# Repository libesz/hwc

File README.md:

# Hot Water Circulation with AVR

## The problem
This is a tiny project to control a water pump. In a typical domestic hot water system, there is a common problem that the water gets cold in the pipes if some faucets are too far. So you have to waste a lot of water (and time :) ) until you get the hot water, if is was not used recently.

The base of the solution is to build also a returning pipe between the last faucet and the boiler or hot water tank, where a pump can circulate the returning water, so that keeping the pipes hot.

The big question is that based on what event are you going to circulate the water? After a bit of googling you can find these ideas:
* Timer switch, programmed for the typical hot water use times (morning, evening).
* Thermostat: you somehow measure the returning water's temperature and control the pump when needed.
* Detect water usage: there are solutions which can detect when you use any faucet in the house. So you can trigger the circulation by using the e.g. shower for a second, than wait until the hot water arrive before you really start to use it.

## Solution
I was not impressed by any of the solutions above, even not with any combinations. Fortunately I had the pump and the returning pipe built in, so I can control it how I want.
My solution is based on the detection of motion in the house. I have a basic alarm system in the house with passive IR motion sensors in every rooms. The idea is that before every water usage, the people have to walk to the desired faucet. There might be additional time before you need the hot water, like you use the toilet first, for instance :). This time is most probably enough for the pump to get hot water everywhere.
I inspected my alarm system and found a programmable output on the board which can follow any selection of the motion sensors status, so it can trigger this AVR project, which will control the pump for a predefined time.
Also there is a hold timer, which will not switch on the pump ON again if the water is supposed to be still hot in the pipe.

The code is written in C++ and using my base library [from here](https://github.com/libesz/AvrCppBaseLib).

### HW:
* ATTINY45@1MHz
* Opto couplers for both input from the alarm system and towards the output
* 12V relay to control the pump

## Project documentation:
[Link](http://libesz.digitaltrip.hu/automatic-how-water-circulator/)

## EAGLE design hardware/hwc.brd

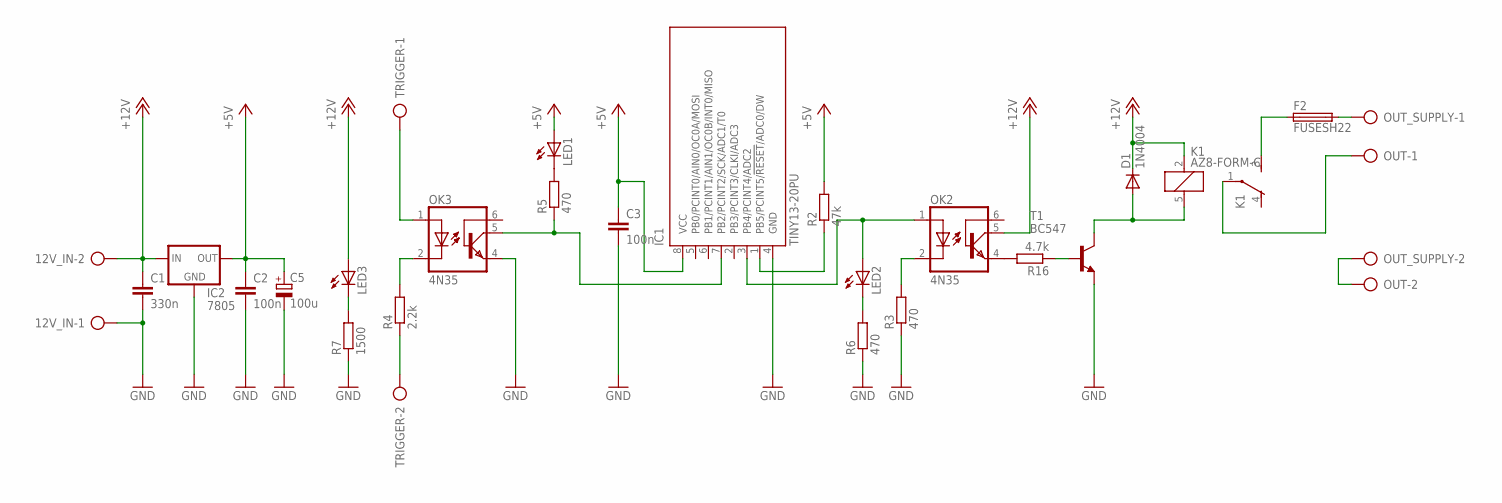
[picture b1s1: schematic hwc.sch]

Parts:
12V_IN: AK300/2
C1: 330n; C050-025X075
C2, C3: 100n; C050-025X075
C5: 100u; E5-8,5
D1: 1N4004; DO41-10
F2: FUSESH22; SH22
IC1: TINY13-20PU; DIL08
IC2: 7805; 78XXL
K1: AZ8-FORM-C; AZ8
LED1, LED2, LED3: LED5MM
OK2, OK3: 4N35; DIL06
OUT: AK300/2
OUT_SUPPLY: AK300/2
R2: 47k; 0204/7
R3, R5, R6: 470; 0204/7
R4: 2.2k; 0204/7
R7: 1500; 0204/7
R16: 4.7k; 0204/7
T1: BC547; TO92
TRIGGER: AK300/2

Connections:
+5V: C2.1, C3.1, C5.+, IC1.8 (VCC), IC2.OUT, LED1.A, R2.2
+12V: 12V_IN.2, C1.1, D1.C, IC2.IN, K1.2 (1), LED3.A, OK2.5 (COL)
GND: 12V_IN.1, C1.2, C2.2, C3.2, C5.-, IC1.4 (GND), IC2.GND, OK3.4 (EMI), R3.1, R6.1, R7.1, T1.1 (E)
unnamed: IC1.1 (PB5/PCINT5/!RESET!/ADC0/DW), R2.1
unnamed: LED1.K (C), R5.2
unnamed: OUT.2, OUT_SUPPLY.2
unnamed: F2.1, K1.3 (S)
unnamed: K1.1, OUT.1
unnamed: LED2.K (C), R6.2
unnamed: LED3.K (C), R7.2
unnamed: OK2.2 (C), R3.2
unnamed: IC1.3 (PB4/PCINT4/ADC2), LED2.A, OK2.1 (A)
unnamed: F2.2, OUT_SUPPLY.1
unnamed: OK3.2 (C), R4.2
unnamed: OK3.1 (A), TRIGGER.1
unnamed: R4.1, TRIGGER.2
unnamed: IC1.7 (PB2/PCINT2/SCK/ADC1/T0), OK3.5 (COL), R5.1
unnamed: OK2.4 (EMI), R16.2
unnamed: D1.A, K1.5 (2), T1.3 (C)
unnamed: R16.1, T1.2 (B)

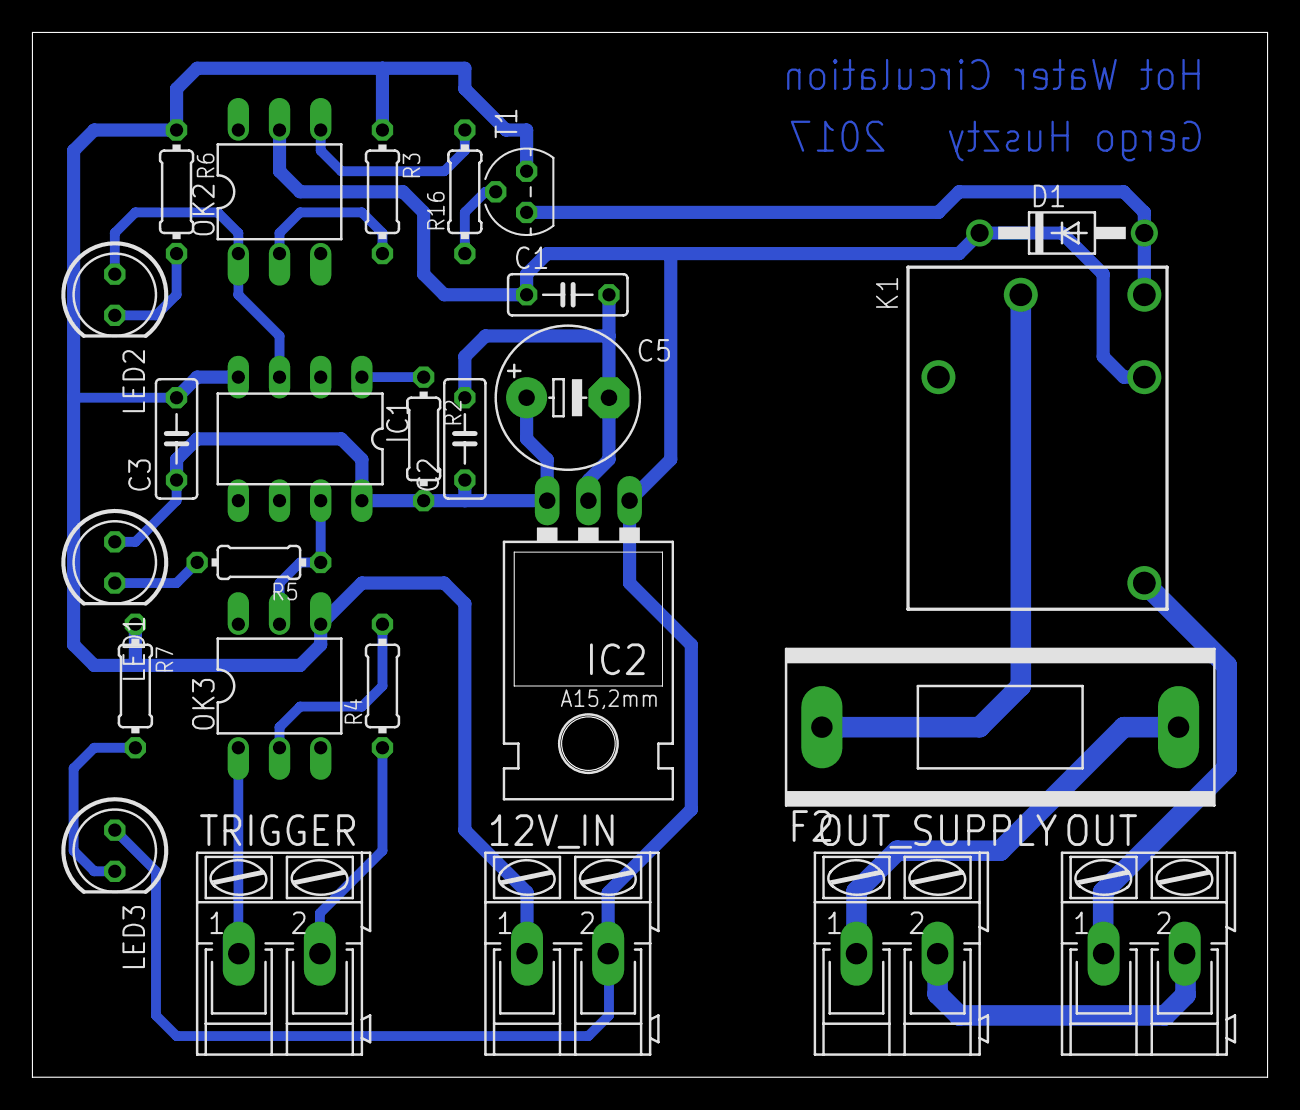
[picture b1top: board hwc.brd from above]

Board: 2 copper layers, 76.2 x 64.4 mm, 26 parts (0 on the bottom side), 20 nets.

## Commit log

2017-02-26 Initial commit for Hot Water Circulating PoC project - it uses AvrCppBaseLib
2017-02-26 BlinkingLed renamed to TimedOutput
2017-02-26 output is now PORTB2 to have INT0 external interrupt
2017-02-26 facing in timer interrupt
2017-02-26 #define for mask
2017-02-26 SoftTimerSet is now a template
2017-02-26 indentation fixed
2017-02-26 README added.
2017-02-26 ON timer changed to 2 minutes.
2017-05-27 OUTPUT port changed
2017-05-27 timers adjusted (5 mins for output, 25 mins hold-off)
2017-05-27 schematic and board added
2017-05-27 README facing
2017-05-27 Project link added.
